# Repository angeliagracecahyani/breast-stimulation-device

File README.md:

# breast-stimulation-device
This repository contains the design file summary of the breast engorgement project.

The schematic design and PCB files can be accessed at:

https://github.com/angeliagracecahyani/breast-stimulation-device/blob/main/Projek%202.kicad_sch

https://github.com/angeliagracecahyani/breast-stimulation-device/blob/main/Projek%202.kicad_pcb

The ESP32 program code is available at:

https://github.com/angeliagracecahyani/breast-stimulation-device/blob/main/BreastEngorgementdvce_HardwareCode.ino

The device interface application can be accessed at:

https://github.com/angeliagracecahyani/breast-stimulation-device/blob/main/ESP32Bluetooth%20(1).apk

https://github.com/angeliagracecahyani/breast-stimulation-device/blob/main/ESP32Bluetooth.aab

https://github.com/angeliagracecahyani/breast-stimulation-device/blob/main/ESP32Bluetooth.aia

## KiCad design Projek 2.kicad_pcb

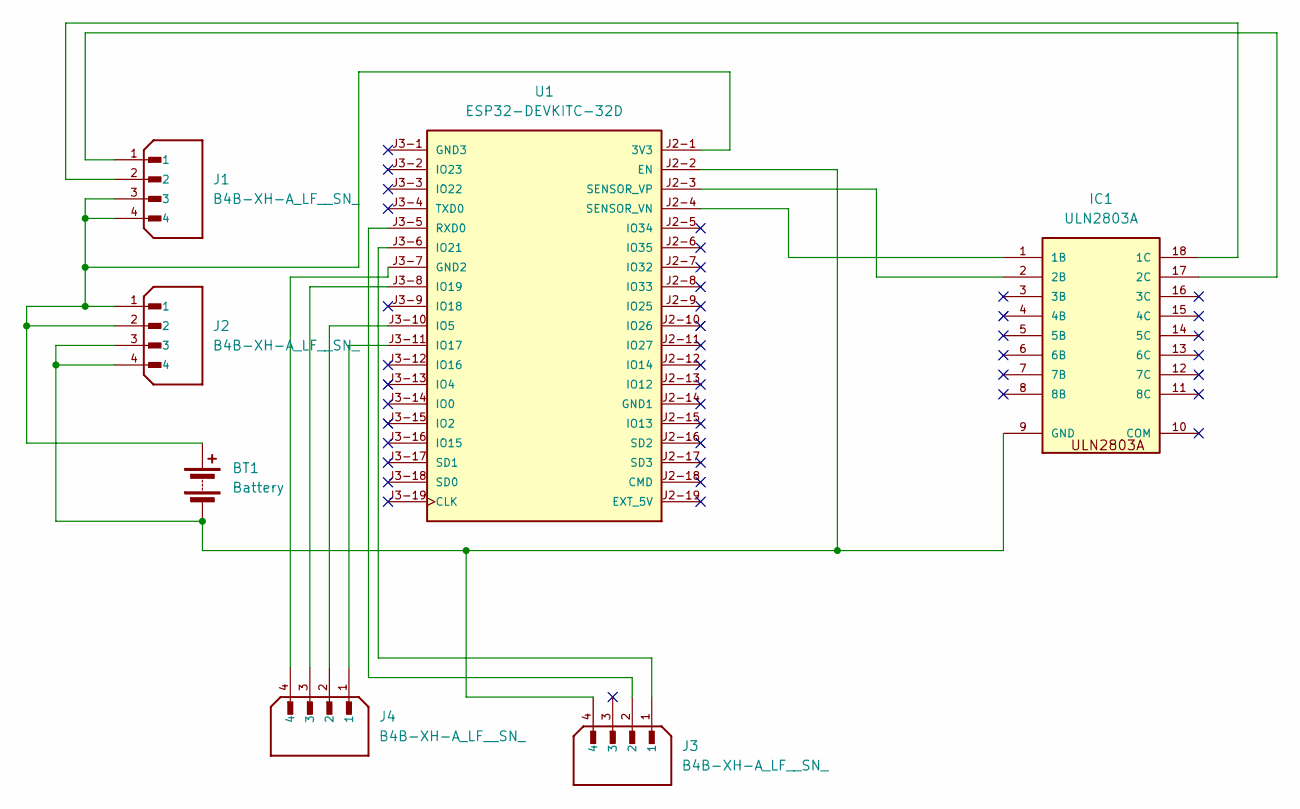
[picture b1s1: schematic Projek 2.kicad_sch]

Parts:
BT1: Battery; BatteryHolder_Keystone_2998_1x6.8mm
IC1: ULN2803A
J1, J2, J3, J4: B4B-XH-A_LF__SN_; JST_B4B-XH-A_LF__SN_; PARTREV 7/4/21
U1: ESP32-DEVKITC-32D; MODULE_ESP32-DEVKITC-32D; PARTREV V4

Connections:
unnamed: BT1.1 (+), J1.3, J1.4, J2.1, J2.2, U1.J2-1 (3V3)
unnamed: BT1.2 (-), IC1.9 (GND), J2.3, J2.4, J3.4, U1.J2-2 (EN)
unnamed: IC1.1 (1B), U1.J2-4 (SENSOR_VN)
unnamed: IC1.18 (1C), J1.2
unnamed: IC1.2 (2B), U1.J2-3 (SENSOR_VP)
unnamed: IC1.17 (2C), J1.1
unnamed: J4.4, U1.J3-7 (GND2)
unnamed: J4.2, U1.J3-10 (IO5)
unnamed: J4.1, U1.J3-11 (IO17)
unnamed: J4.3, U1.J3-8 (IO19)
unnamed: J3.1, U1.J3-6 (IO21)
unnamed: J3.2, U1.J3-5 (RXD0)

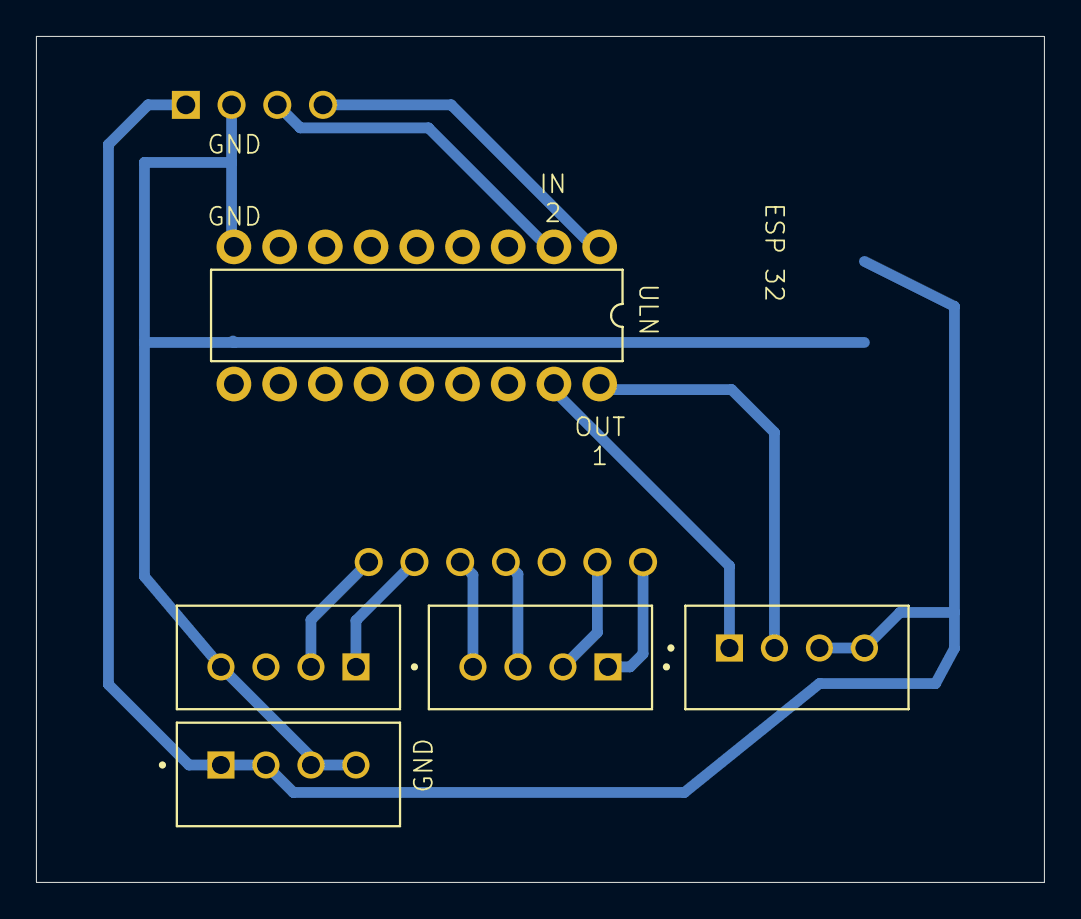
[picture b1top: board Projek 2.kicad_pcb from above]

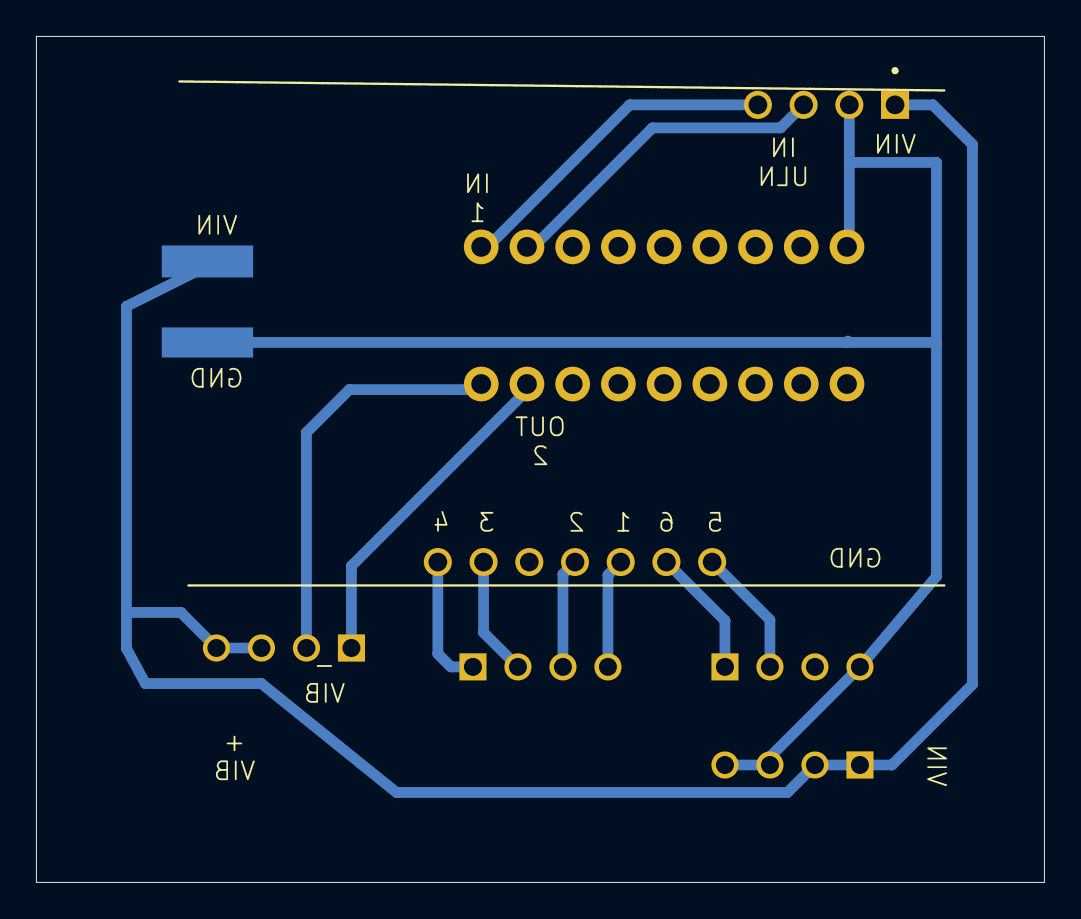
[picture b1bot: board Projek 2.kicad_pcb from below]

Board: 2 copper layers, 56.0 x 47.0 mm, 7 parts (2 on the bottom side), 12 nets.

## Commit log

2026-04-25 Update README with project details and resources
    Added project summary and links for design files and code.
2026-04-25 Update README with device interface application links
    Add links to the device interface application in README
2026-04-25 Update LICENSE
